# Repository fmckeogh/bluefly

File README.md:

# bluefly

> BLE-based light electric vehicle control system

## Building

TODO

## Components

* nRF52810 microcontrollers
* SSD1306 display
* NCR18650GA battery
* Hall-effect thumb control

## TODO

### Software

* [ ] MVP (move thumb and motor spins as a result)
* [ ] Proper BLE connection
* [ ] Display telemetry
* [ ] Transparent passthrough to VESC for configuration from PC/phone
* [ ] CLI for configuring remote/receiver
* [ ] OTA firmware updates of remote and receiver
* [ ] Battery percent on phone
* [ ] HomeKit integration

### Hardware

* [X] Finalise breadboard design of both remote and receiver
* [x] Initial PCB design and order of both remote and receiver
* [ ] Case design

## Contributing

Issues and PRs very welcome :)

## License

Mozilla Public License Version 2.0([LICENSE](LICENSE) or
  https://www.mozilla.org/en-US/MPL/2.0/)

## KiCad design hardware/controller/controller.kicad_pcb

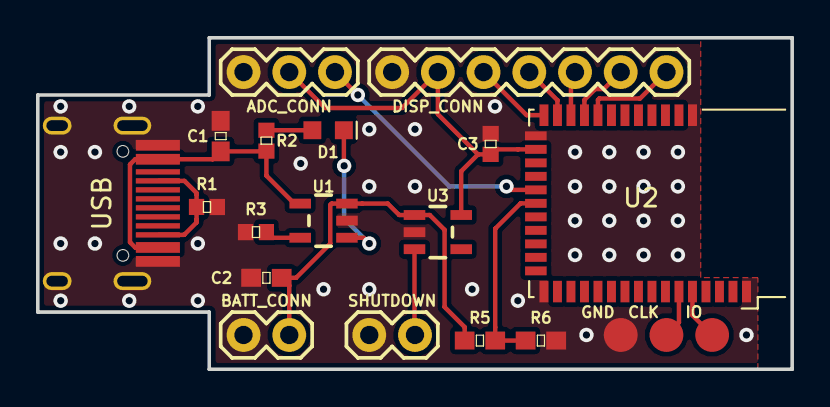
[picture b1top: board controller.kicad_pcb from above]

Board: 2 copper layers, 41.9 x 18.4 mm, 20 parts (0 on the bottom side), 18 nets.

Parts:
C1, C2: 4.7UF; 0603
C3: 1.0UF-0402-16V-10%; 0402
D1: LED-BLUE0603; LED-0603
J1: ADC_CONN; 1X03
J2: DISP_CONN; 1X07
J3: BATT_CONN; 1X02
J4: SHUTDOWN; 1X02
R1: 5.1K; 0402
R2: RESISTOR0402; 0402
R3: 2K; 0402
R5, R6: 1MOHM-0603-1_4W-5%; 0603
SWD_CLK1: CLK; PAD.03X.05
SWD_GND1: GND; PAD.03X.05
SWD_IO1: IO; PAD.03X.05
U1: MCP73831; SOT23-5
U2: BL652; Laird_BL652
U3: TC1014; SOT23-5
USB: HRO-TYPE-C-31-M-12; HRO-TYPE-C-31-M-12-HandSoldering_modified

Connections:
/AIN0: J1.3, U2.23
/AIN1: R5.2, R6.1, U2.22
/CC: R1.1, USB.4, USB.10
/CS: J2.7, U2.32
/DC: J2.5, U2.30
/MOSI: J2.3, U2.28
/RST: J2.6, U2.31
/SCK: J2.4, U2.29
/SWDCLK: SWD_CLK1.P$1, U2.6
/SWDIO: SWD_IO1.P$1, U2.5
GND: C1.2, C2.2, C3.2, J1.1, J2.1, J3.1, J4.2, R1.2, R3.2, R6.2, SWD_GND1.P$1, U1.2, U2.1, U2.16, U2.27, U2.39, U3.2, USB.1, USB.12, USB.13
unnamed: D1.A, R2.1
unnamed: D1.C, U1.1
unnamed: J4.1, U3.3
unnamed: R3.1, U1.5
VCC: C3.1, J1.2, J2.2, U2.26, U3.5
V_BATT: C2.1, J3.2, R5.1, U1.3, U3.1
V_USB: C1.1, R2.2, U1.4, USB.2, USB.11

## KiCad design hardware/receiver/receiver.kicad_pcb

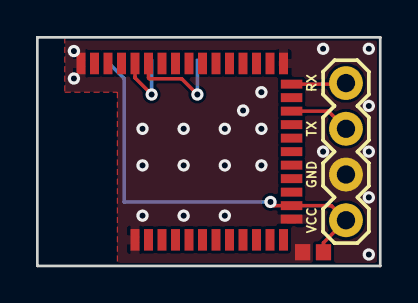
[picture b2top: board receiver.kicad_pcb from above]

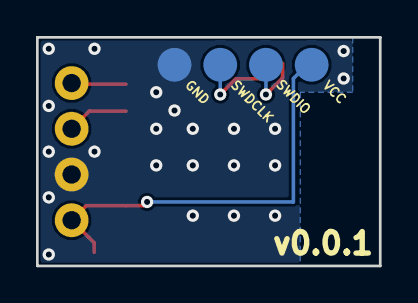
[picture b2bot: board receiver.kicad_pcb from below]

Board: 2 copper layers, 19.0 x 12.7 mm, 5 parts (4 on the bottom side), 2 nets.

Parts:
C1: 0.1UF-0402-16V-10%; 0402_mod
GND1: TEST-POINT3; PAD.03X.05
SWDCLK1: TEST-POINT3; PAD.03X.05
SWDIO1: TEST-POINT3; PAD.03X.05
VCC1: TEST-POINT3; PAD.03X.05

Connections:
GND: C1.2, GND1.P$1
VCC: C1.1, VCC1.P$1

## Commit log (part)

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2018-03-10 blinks
2018-03-10 SSD1306 working
2018-03-31 SSD1306 now working
2018-03-31 Fixed TODO checkboxes
2018-03-31 Actually fixed checkboxes :|
2018-03-31 Removed graphics feature as it is on by default now
2018-03-31 Travis CI banner
2018-03-31 Misc README tidy up
2018-03-31 Testing Travis
2018-03-31 Fixed cargo config for all targets
2018-04-02 Locking ssd1306, embedded-graphics to known good commit
2018-04-27 Update Travis badge URL
2018-04-27 RTFM and SYS_TICK working
2018-04-27 Remove unnessary flushes
2018-05-02 Add empty PCB files
2018-05-02 Update ssd1306 lib version
2018-05-02 Fix readme grammar
2018-05-02 Change planned remote design
2018-05-06 Add alloc-cortex-m heap allocator
2018-05-06 Switch to known-good nightly
2018-05-06 Create write_display function
2018-05-06 Ran cargo fmt
2018-05-12 Broken, SPI display
2018-05-12 General tidy up
2018-05-12 Update CI rust nightly version
2018-05-13 More tidy up
2018-05-13 Refactored display code
2018-05-13 Started work on battery icon, embedded-icons crate?
2018-05-13 Change license
2018-05-13 Added remote battery icon
2018-05-13 Added signal indicator
2018-05-13 Removed unused build targets from CI
2018-05-13 Trying a new signal design
2018-05-13 Working on external interrupt
2018-05-14 Improve release build profile
2018-05-14 Improve build process
2018-05-14 Forgot to stage .travis.yml
2018-05-14 Fix Travis
2018-05-14 Removed checksumming as rustc is not deterministic
2018-05-14 Interrupt still not working :(
2018-06-07 Update panic-abort requirement to 0.2.0
    Updates the requirements on [panic-abort](https://github.com/japaric/panic-abort) to permit the latest version.
    - [Release notes](https://github.com/japaric/panic-abort/releases)
    - [Changelog](https://github.com/japaric/panic-abort/blob/master/CHANGELOG.md)
    - [Commits](https://github.com/japaric/panic-abort/commits/v0.2.0)
2018-06-07 Update cortex-m requirement to 0.5.2
    Updates the requirements on [cortex-m](https://github.com/japaric/cortex-m) to permit the latest version.
    - [Release notes](https://github.com/japaric/cortex-m/releases)
    - [Changelog](https://github.com/japaric/cortex-m/blob/master/CHANGELOG.md)
    - [Commits](https://github.com/japaric/cortex-m/commits/v0.5.2)
2018-06-22 Writing to backup registers is working! :)
2018-07-03 Successfully writing magic bits to backup register
2018-07-03 Updating versions and Makefile
2018-07-14 Fix README
2018-07-19 Communication between controller and receiver working
2018-07-19 fmt and clippy
2018-07-19 Cargo fmt
2018-07-19 Fix dependency source
2018-07-23 MVP reached
2018-07-23 Empty hardware projects
2018-07-24 Change to 433MHz to match antennae
2018-07-24 Initial case design
2018-07-25 New case design
2018-07-25 Added sensor, display and USB to case
2018-08-12 Started ugly case design
2018-08-12 Started PCB design
2018-08-12 Add Dependabot badge
2018-08-12 Update embedded-graphics requirement from 0.1.1 to 0.3.0
    Updates the requirements on [embedded-graphics](https://github.com/jamwaffles/embedded-graphics) to permit the latest version.
    - [Release notes](https://github.com/jamwaffles/embedded-graphics/releases)
    - [Commits](https://github.com/jamwaffles/embedded-graphics/commits/0.3.0)
2018-09-03 Update embedded-graphics requirement from 0.1.1 to 0.4.0
    Updates the requirements on [embedded-graphics](https://github.com/jamwaffles/embedded-graphics) to permit the latest version.
    - [Release notes](https://github.com/jamwaffles/embedded-graphics/releases)
    - [Commits](https://github.com/jamwaffles/embedded-graphics/commits/0.4.0)
2018-09-10 Update cortex-m-rt requirement from 0.5.1 to 0.6.3
    Updates the requirements on [cortex-m-rt](https://github.com/rust-embedded/cortex-m-rt) to permit the latest version.
    - [Release notes](https://github.com/rust-embedded/cortex-m-rt/releases)
    - [Changelog](https://github.com/rust-embedded/cortex-m-rt/blob/master/CHANGELOG.md)
    - [Commits](https://github.com/rust-embedded/cortex-m-rt/commits/v0.6.3)
2018-09-10 Update panic-semihosting requirement from 0.3.0 to 0.5.0
    Updates the requirements on [panic-semihosting](https://github.com/rust-embedded/panic-semihosting) to permit the latest version.
    - [Release notes](https://github.com/rust-embedded/panic-semihosting/releases)
    - [Changelog](https://github.com/rust-embedded/panic-semihosting/blob/master/CHANGELOG.md)
    - [Commits](https://github.com/rust-embedded/panic-semihosting/commits/v0.5.0)
2018-10-01 Update cortex-m-rt requirement from 0.5.1 to 0.6.4
    Updates the requirements on [cortex-m-rt](https://github.com/rust-embedded/cortex-m-rt) to permit the latest version.
    - [Release notes](https://github.com/rust-embedded/cortex-m-rt/releases)
    - [Changelog](https://github.com/rust-embedded/cortex-m-rt/blob/master/CHANGELOG.md)
    - [Commits](https://github.com/rust-embedded/cortex-m-rt/commits/v0.6.4)
2018-10-15 Update embedded-graphics requirement from 0.1.1 to 0.4.1
    Updates the requirements on [embedded-graphics](https://github.com/jamwaffles/embedded-graphics) to permit the latest version.
    - [Release notes](https://github.com/jamwaffles/embedded-graphics/releases)
    - [Commits](https://github.com/jamwaffles/embedded-graphics/commits/0.4.1)
2018-10-22 Update embedded-graphics requirement from 0.1.1 to 0.4.3
    Updates the requirements on [embedded-graphics](https://github.com/jamwaffles/embedded-graphics) to permit the latest version.
    - [Release notes](https://github.com/jamwaffles/embedded-graphics/releases)
    - [Commits](https://github.com/jamwaffles/embedded-graphics/commits)
2018-10-29 Update embedded-graphics requirement from 0.1.1 to 0.4.4
    Updates the requirements on [embedded-graphics](https://github.com/jamwaffles/embedded-graphics) to permit the latest version.
    - [Release notes](https://github.com/jamwaffles/embedded-graphics/releases)
    - [Commits](https://github.com/jamwaffles/embedded-graphics/commits/0.4.4)
2018-10-29 Update panic-semihosting requirement from 0.3.0 to 0.5.1
    Updates the requirements on [panic-semihosting](https://github.com/rust-embedded/panic-semihosting) to permit the latest version.
    - [Release notes](https://github.com/rust-embedded/panic-semihosting/releases)
    - [Changelog](https://github.com/rust-embedded/panic-semihosting/blob/master/CHANGELOG.md)
    - [Commits](https://github.com/rust-embedded/panic-semihosting/commits/v0.5.1)
2018-12-10 Update cortex-m-rt requirement from 0.5.1 to 0.6.6
    Updates the requirements on [cortex-m-rt](https://github.com/rust-embedded/cortex-m-rt) to permit the latest version.
    - [Release notes](https://github.com/rust-embedded/cortex-m-rt/releases)
    - [Changelog](https://github.com/rust-embedded/cortex-m-rt/blob/master/CHANGELOG.md)
    - [Commits](https://github.com/rust-embedded/cortex-m-rt/commits/v0.6.6)
2018-12-17 Update cortex-m-rt requirement from 0.5.1 to 0.6.7
    Updates the requirements on [cortex-m-rt](https://github.com/rust-embedded/cortex-m-rt) to permit the latest version.
    - [Release notes](https://github.com/rust-embedded/cortex-m-rt/releases)
    - [Changelog](https://github.com/rust-embedded/cortex-m-rt/blob/master/CHANGELOG.md)
    - [Commits](https://github.com/rust-embedded/cortex-m-rt/commits/v0.6.7)
2018-12-24 Update embedded-graphics requirement from 0.1.1 to 0.4.5
    Updates the requirements on [embedded-graphics](https://github.com/jamwaffles/embedded-graphics) to permit the latest version.
    - [Release notes](https://github.com/jamwaffles/embedded-graphics/releases)
    - [Commits](https://github.com/jamwaffles/embedded-graphics/commits/embedded-graphics-0.4.5)
2019-02-08 refactor: RTFM rewrite
2019-02-10 remove radios and add adc
2019-02-11 Bump vesc-comm from 0.1.0 to 0.1.1
    Bumps [vesc-comm](https://github.com/chocol4te/vesc-comm) from 0.1.0 to 0.1.1.
    - [Release notes](https://github.com/chocol4te/vesc-comm/releases)
    - [Commits](https://github.com/chocol4te/vesc-comm/commits)
2019-02-18 Bump ssd1306 from 0.2.2 to 0.2.3
    Bumps [ssd1306](https://github.com/jamwaffles/ssd1306) from 0.2.2 to 0.2.3.
    - [Release notes](https://github.com/jamwaffles/ssd1306/releases)
    - [Commits](https://github.com/jamwaffles/ssd1306/compare/0.2.2...ssd1306-0.2.3)
2019-02-18 Bump cortex-m-rtfm from 0.4.0 to 0.4.1
    Bumps [cortex-m-rtfm](https://github.com/japaric/cortex-m-rtfm) from 0.4.0 to 0.4.1.
    - [Release notes](https://github.com/japaric/cortex-m-rtfm/releases)
    - [Changelog](https://github.com/japaric/cortex-m-rtfm/blob/master/CHANGELOG.md)
    - [Commits](https://github.com/japaric/cortex-m-rtfm/compare/v0.4.0...v0.4.1)
2019-02-19 feat: add hardware
2019-02-19 feat: rtfm on nrf modules
2019-02-21 docs: add mcu and module datasheets
2019-02-21 test: 2 stage CI
2019-02-21 fix: remove kicad deps and bad case design
2019-02-23 feat: finish controller pcb
2019-02-27 Bump cortex-m-rtfm from 0.4.1 to 0.4.2
    Bumps [cortex-m-rtfm](https://github.com/japaric/cortex-m-rtfm) from 0.4.1 to 0.4.2.
    - [Release notes](https://github.com/japaric/cortex-m-rtfm/releases)
    - [Changelog](https://github.com/japaric/cortex-m-rtfm/blob/master/CHANGELOG.md)
    - [Commits](https://github.com/japaric/cortex-m-rtfm/compare/v0.4.1...v0.4.2)
2019-03-02 Bump ssd1306 from 0.2.3 to 0.2.4
    Bumps [ssd1306](https://github.com/jamwaffles/ssd1306) from 0.2.3 to 0.2.4.
    - [Release notes](https://github.com/jamwaffles/ssd1306/releases)
    - [Commits](https://github.com/jamwaffles/ssd1306/compare/ssd1306-0.2.3...0.2.4)
2019-03-03 Bump embedded-graphics from 0.4.5 to 0.4.7
    Bumps [embedded-graphics](https://github.com/jamwaffles/embedded-graphics) from 0.4.5 to 0.4.7.
    - [Release notes](https://github.com/jamwaffles/embedded-graphics/releases)
    - [Commits](https://github.com/jamwaffles/embedded-graphics/compare/embedded-graphics-0.4.5...embedded-graphics-0.4.7)
2019-03-05 chore: rename project
2019-03-05 feat: build on stable
2019-03-16 start using beacons for hacky mvp
2019-03-20 feat: ADC working
2019-03-28 test: add ci
2019-03-28 docs: add tokei badge
2019-03-29 chore(deps): bump uuid from 0.7.2 to 0.7.4
    Bumps [uuid](https://github.com/uuid-rs/uuid) from 0.7.2 to 0.7.4.
    - [Release notes](https://github.com/uuid-rs/uuid/releases)
    - [Commits](https://github.com/uuid-rs/uuid/compare/0.7.2...0.7.4)
2019-03-29 chore: remove unused dep
2019-04-03 chore(deps): bump cortex-m-rt from 0.6.7 to 0.6.8
    Bumps [cortex-m-rt](https://github.com/rust-embedded/cortex-m-rt) from 0.6.7 to 0.6.8.
    - [Release notes](https://github.com/rust-embedded/cortex-m-rt/releases)
    - [Changelog](https://github.com/rust-embedded/cortex-m-rt/blob/master/CHANGELOG.md)
    - [Commits](https://github.com/rust-embedded/cortex-m-rt/commits)
2019-04-17 feat: potentiometer control of VESC over BLE working
2019-04-18 fix: controller ADC scaling
2019-04-19 refactor: use BeaconScanner in receiver
2019-04-19 ci: switch to beta until https://github.com/rust-lang/rust/pull/58605 is resolved
2019-04-19 ci: release build instead
2019-04-19 ci: releases
2019-04-22 chore(deps): bump nb from 0.1.1 to 0.1.2
    Bumps [nb](https://github.com/japaric/nb) from 0.1.1 to 0.1.2.
    - [Release notes](https://github.com/japaric/nb/releases)
    - [Changelog](https://github.com/japaric/nb/blob/v0.1.2/CHANGELOG.md)
    - [Commits](https://github.com/japaric/nb/compare/v0.1.1...v0.1.2)
2019-04-22 chore(deps): bump cortex-m-rtfm from 0.4.2 to 0.4.3
    Bumps [cortex-m-rtfm](https://github.com/japaric/cortex-m-rtfm) from 0.4.2 to 0.4.3.
    - [Release notes](https://github.com/japaric/cortex-m-rtfm/releases)
    - [Changelog](https://github.com/japaric/cortex-m-rtfm/blob/master/CHANGELOG.md)
    - [Commits](https://github.com/japaric/cortex-m-rtfm/compare/v0.4.2...v0.4.3)
